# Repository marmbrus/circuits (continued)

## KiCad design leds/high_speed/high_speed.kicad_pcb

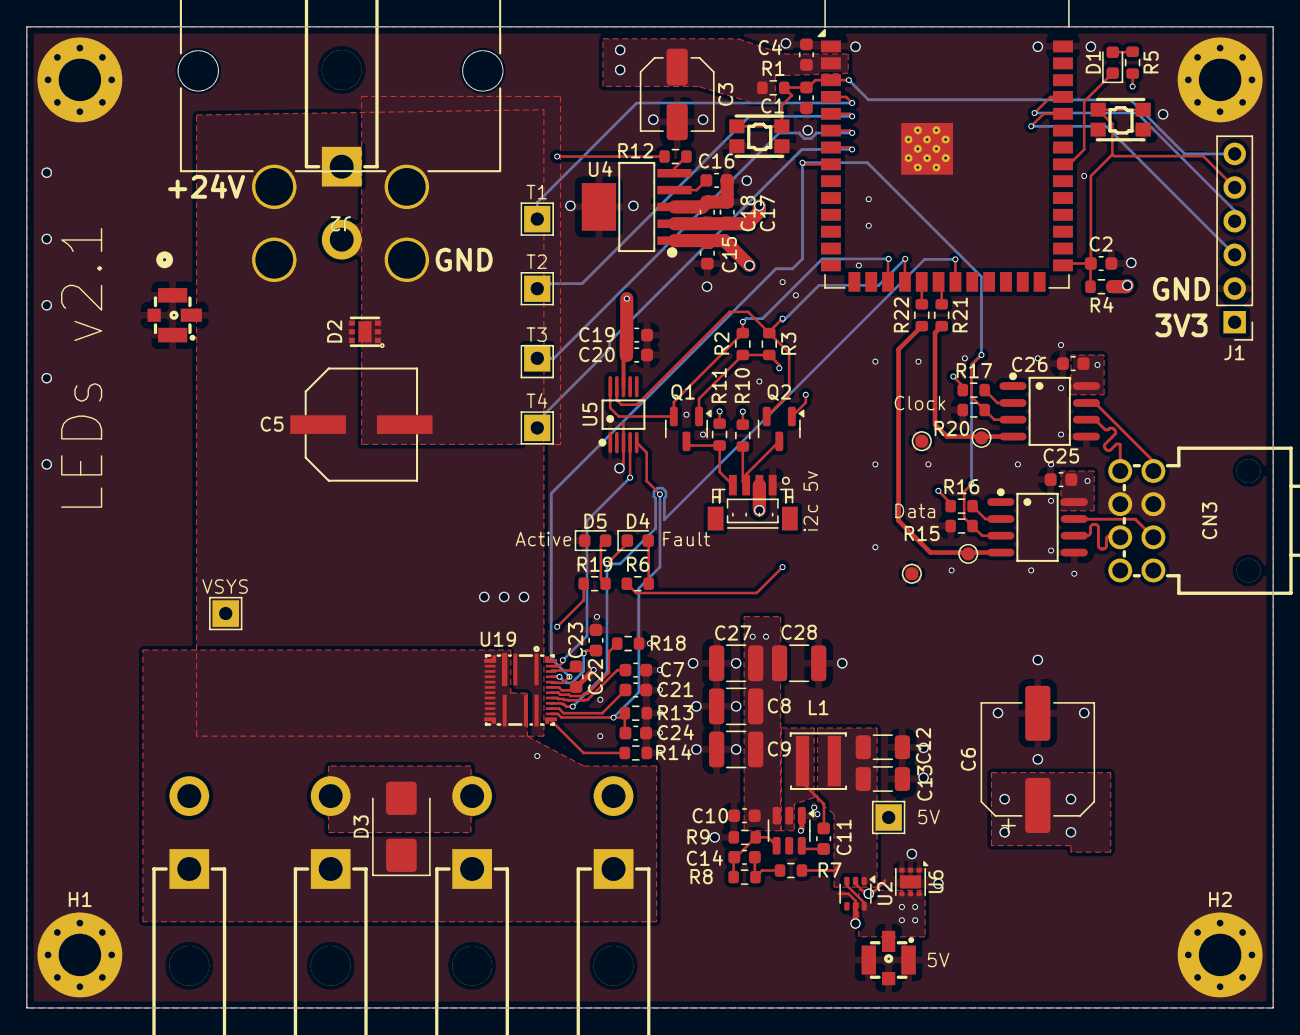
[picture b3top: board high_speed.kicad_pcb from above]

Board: 4 copper layers, 94.0 x 74.0 mm, 94 parts (0 on the bottom side), 48 nets.

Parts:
C1: 10uf; C_0603_1608Metric
C2: 1uf; C_0603_1608Metric
C3: 22uF; C_Elec_5x5.8
C4, C7, C10, C20, C24, C25, C26: 100nF; C_0603_1608Metric
C5: 220uF; CAP-SMD_BD8.0-L8.3-W8.3-FD
C6: C_Polarized; CP_Elec_8x11.9
C8, C9, C27, C28: 10uF; C_1210_3225Metric
C11: 100nf; C_0603_1608Metric
C12, C13: 22uF; C_1206_3216Metric
C14: 75pF; C_0603_1608Metric
C15, C17, C18, C19: 1uF; C_0603_1608Metric
C16: 10nF; C_0603_1608Metric
C21: 470nF; C_0603_1608Metric
C22, C23: 2.2uF; C_0603_1608Metric
CN1, CN2, CN5, CN6, CN13: 39-30-1020; CONN-TH_2P-P5.50_39-30-1020
CN3: 1053141108; CONN-TH_8P-P2.50_MOLEX_1053141108
CN4: BM04B-SRSS-TB(LF)(SN); CONN-SMD_BM04B-SRSS-TB
D1, D4, D5: LED; LED_0603_1608Metric
D2: TVS2700DRVR; WSON-6_L2.0-W2.0-P0.65-BL-EP
D3: D_TVS; D_SMB
H1, H2, H3, H4: MountingHole_Pad; MountingHole_3.2mm_M3_Pad_Via
J1: Conn_01x06; PinHeader_1x06_P2.54mm_Vertical
J2: 428202214; CONN_SDA-42820-0002_02_RC_MOL
L1: XAL4040-103MEC; IND-SMD_L4.0-W4.0-A
Q1, Q2: BSS138; SOT-23
R1, R2, R3, R4, R10, R11, R12, R15, R16, R17, R19, R20: 10k; R_0603_1608Metric
R5: 330; R_0603_1608Metric
R6: 1k; R_0603_1608Metric
R7: 49.9; R_0603_1608Metric
R8: 100k; R_0603_1608Metric
R9: 13.3k; R_0603_1608Metric
R13, R14: 3.6k; R_0603_1608Metric
R18: 53.6k; R_0603_1608Metric
R21, R22: 20; R_0603_1608Metric
RF1, RF2: 73412-0110; ANT-SMD_73412-0110
SW1, SW3: EVPAA602W; KEY-TH_4P-L3.5-W4.9-P2.80-LS4.3
TP1, TP6, TP7, TP8, TP9, TP14: LabeledTestPoint
TP2, TP3, TP4, TP5: TestPoint; TestPoint_Pad_D1.0mm
U1: ESP32-S3-WROOM-1
U2: LM66100DCK; SOT-363_SC-70-6
U3: TPS54202DDC; SOT-23-6
U4: TPS73733DCQ_C5220270; SOT-223-6_L6.5-W3.5-P1.27-LS7.0-BR
U5: ADS1115IDGSR; MSOP-10_L3.0-W3.0-P0.50-LS5.0-BL
U6: TVS0500DRV; WSON-6-1EP_2x2mm_P0.65mm_EP1x1.6mm
U7, U17: THVD2450DR; SOIC-8_L4.9-W3.9-P1.27-LS6.0-BL
U19: MP5048GU-Z; QFN-30_L5.0-W5.0-P0.40-TL_MP5048GU-Z

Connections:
/3v3/3v3: C3.1, C4.1, C17.1, C18.1, C25.1, C26.1, J1.1, Q1.1 (G), Q2.1 (G), R1.1, R2.1, R3.1, R4.1, R5.2, R6.1, R16.1, R17.1, U1.2 (3V3), U4.2 (OUT), U7.8 (VCC), U17.8 (VCC)
/5V: C6.1, C15.1, C19.1, C20.1, CN4.2, R10.1, R11.1, R12.1, RF2.2 (SIG), U2.3 (~CE), U2.6 (VOUT), U4.1 (IN), U5.8 (VDD), U6.4 (IN), U6.5 (IN), U6.6 (IN)
/VSYS: C5.1, C8.1, C9.1, C10.1, C27.1, C28.1, CN6.1, D2.4 (IN), D2.5 (IN), D2.6 (IN), J2.1_1, J2.1_2, RF1.2 (SIG), TP1.1, U3.3 (VIN), U19.1 (VIN), U19.2 (VIN), U19.18 (VIN)
/a2d/AIN1: U5.4 (AIN0), U19.29 (VTEMP)
/a2d/AIN2: C24.1, R13.1, U5.5 (AIN1), U19.20 (IMON)
/a2d/I2C.SCL: Q1.2 (S), R2.2, U1.17 (IO9), U5.10 (SCL)
/a2d/I2C.SDA: Q2.2 (S), R3.2, U1.18 (IO10), U5.9 (SDA)
/buckconverter/FB: C14.1, R8.2, R9.1, U3.4 (FB)
/buckconverter/SW: C11.2, L1.1, U3.2 (SW)
/esp32/EN1: R15.1, R20.1, U1.8 (IO15), U7.3 (DE), U17.3 (DE), U19.26 (ON)
/esp32/Fault: D4.1 (K), U1.21 (IO13), U19.22 (FAULT)
/esp32/LEDCLOCK: R21.2, TP2.1, U7.4 (D)
/esp32/LEDDATA: R22.2, TP3.1, U17.4 (D)
/esp32/T1: TP6.1, U1.4 (IO4)
/esp32/T2: TP7.1, U1.5 (IO5)
/esp32/T3: TP8.1, U1.6 (IO6)
/esp32/T4: TP9.1, U1.7 (IO7)
/led_channel/RS485/A: CN3.3, U17.6 (A)
/led_channel/RS485/B: CN3.7, U17.7 (B)
/led_channel/RS486/A: CN3.1, U7.6 (A)
/led_channel/RS486/B: CN3.5, U7.7 (B)
/led_channel/VLED: CN1.1, CN2.1, CN3.4, CN3.8, CN5.1, CN13.1, D3.1 (K), R19.1, U19.3 (VOUT), U19.4 (VOUT), U19.5 (VOUT), U19.6 (VOUT), U19.7 (VOUT), U19.8 (VOUT), U19.9 (VOUT), U19.10 (VOUT), U19.11 (VOUT), U19.12 (VOUT), U19.13 (VOUT), U19.14 (VOUT), U19.15 (VOUT), U19.16 (VOUT), U19.17 (VOUT)
GND: C1.2, C2.2, C3.2, C4.2, C5.2, C6.2, C7.2, C8.2, C9.2, C10.2, C12.2, C13.2, C15.2, C16.2, C17.2, C18.2, C19.2, C20.2, C21.2, C22.2, C23.2, C24.2, C25.2, C26.2, C27.2, C28.2, CN1.2, CN2.2, CN3.2, CN3.6, CN4.1, CN5.2, CN6.2, CN13.2, D2.1 (GND), D2.2 (GND), D2.3 (GND), D2.7 (GND), D3.2 (A), D5.1 (K), H1.1, H2.1, H3.1, H4.1, J1.2, J2.2_1, J2.2_2, R9.2, R13.2, R14.2, R15.2, R18.2, R20.2, RF1.1 (GND), RF1.3 (GND), RF1.4 (GND), RF2.1 (GND), RF2.3 (GND), RF2.4 (GND), SW1.2, SW1.2', SW3.2, SW3.2', TP4.1, TP5.1, U1.1 (GND), U1.40 (GND), U1.41 (GND), U2.2 (GND), U2.5 (ST), U3.1 (GND), U4.3 (GND), U4.6 (GND), U5.1 (ADDR), U5.3 (GND), U6.1 (GND), U6.2 (GND), U6.3 (GND), U6.7 (GND), U7.5 (GND), U17.5 (GND), U19.25 (GND)
unnamed: C14.2, R7.2, R8.1
unnamed: D1.2 (A), R5.1
unnamed: D1.1 (K), U1.33 (IO40)
unnamed: D4.2 (A), R6.2
unnamed: D5.2 (A), R19.2
unnamed: J1.3, U1.36 (RXD0)
unnamed: J1.4, U1.37 (TXD0)
unnamed: C2.1, J1.5, R4.2, SW3.1, SW3.1', U1.27 (IO0)
unnamed: C1.1, J1.6, R1.2, SW1.1, SW1.1', U1.3 (EN)
unnamed: CN4.4, Q1.3 (D), R11.2
unnamed: CN4.3, Q2.3 (D), R10.2
unnamed: R22.1, U1.19 (IO11)
unnamed: R21.1, U1.20 (IO12)
unnamed: C12.1, C13.1, L1.2, R7.1, TP14.1, U2.1 (VIN)
unnamed: C11.1, U3.6 (BOOT)
unnamed: R12.2, U4.5 (EN)
unnamed: C16.1, U4.4 (NR/FB)
unnamed: R17.2, U7.2 (~RE)
unnamed: R16.2, U17.2 (~RE)
unnamed: C23.1, U19.27 (3V)
unnamed: R18.1, U19.24 (CLREF)
unnamed: R14.1, U19.19 (CS)
unnamed: C21.1, U19.21 (SS)
unnamed: C7.1, U19.23 (TIMER)
unnamed: C22.1, U19.28 (VCC)

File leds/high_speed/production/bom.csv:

Designator,Footprint,Quantity,Value,LCSC Part #
C1,0603,1,10uf,
"C10, C11, C20, C24, C25, C26, C4, C7",0603,8,100nF,
"C12, C13",1206,2,22uF,
C14,0603,1,75pF,
"C15, C17, C18, C19, C2",0603,5,1uF,
C16,0603,1,10nF,
C21,0603,1,470nF,
"C22, C23",0603,2,2.2uF,
"C27, C28, C8, C9",1210,4,10uF,C77102
C3,C_Elec_5x5.8,1,22uF,C336246
C5,CAP-SMD_BD8.0-L8.3-W8.3-FD,1,220uF,C2923769
C6,CP_Elec_8x11.9,1,C_Polarized,C542295
"CN1, CN13, CN2, CN5",CONN-TH_2P-P5.50_39-30-1020,4,39-30-1020,C240832
CN3,CONN-TH_8P-P2.50_MOLEX_1053141108,1,1053141108,C841208
CN4,CONN-SMD_BM04B-SRSS-TB,1,BM04B-SRSS-TB(LF)(SN),C160390
D1,0603,1,LED,C2290
D2,WSON-6_L2.0-W2.0-P0.65-BL-EP,1,TVS2700DRVR,C523797
D3,D_SMB,1,D_TVS,C178227
D4,0603,1,LED,C2286
D5,0603,1,LED,C118334
L1,IND-SMD_L4.0-W4.0-A,1,XAL4040-103MEC,C5144883
"Q1, Q2",SOT-23,2,BSS138,
"R1, R10, R11, R12, R15, R16, R17, R19, R2, R20, R3, R4",0603,12,10k,
"R13, R14",0603,2,3.6k,
R18,0603,1,53.6k,
"R21, R22",0603,2,20,
R5,0603,1,330,
R6,0603,1,1k,
R7,0603,1,49.9,
R8,0603,1,100k,
R9,0603,1,13.3k,
"SW1, SW3",KEY-TH_4P-L3.5-W4.9-P2.80-LS4.3,2,EVPAA602W,C79148
U1,ESP32-S3-WROOM-1,1,ESP32-S3-WROOM-1,C2913202
"U17, U7",SOIC-8_L4.9-W3.9-P1.27-LS6.0-BL,2,THVD2450DR,C2672621
U19,QFN-30_L5.0-W5.0-P0.40-TL_MP5048GU-Z,1,MP5048GU-Z,C3662777
U2,SOT-363_SC-70-6,1,LM66100DCK,
U3,SOT-23-6,1,TPS54202DDC,
U4,SOT-223-6_L6.5-W3.5-P1.27-LS7.0-BR,1,TPS73733DCQ_C5220270,C5220270
U5,MSOP-10_L3.0-W3.0-P0.50-LS5.0-BL,1,ADS1115IDGSR,C37593
U6,WSON-6-1EP_2x2mm_P0.65mm_EP1x1.6mm,1,TVS0500DRV,

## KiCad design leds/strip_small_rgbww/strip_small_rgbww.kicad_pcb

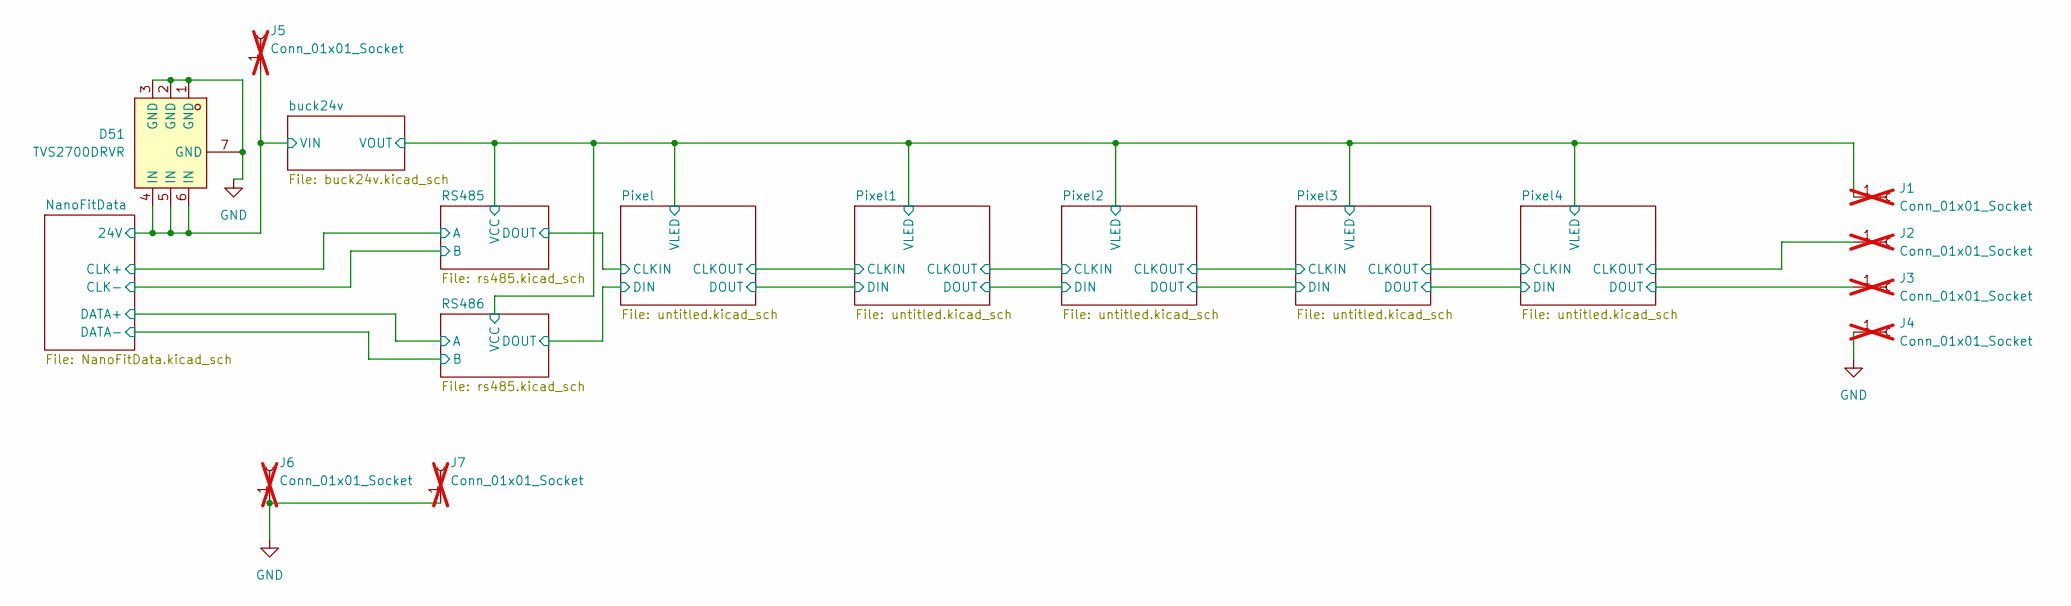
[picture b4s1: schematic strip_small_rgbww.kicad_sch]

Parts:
D51: TVS2700DRVR; WSON-6_L2.0-W2.0-P0.65-BL-EP; LCSC Part C523797
J1, J2, J3, J4, J5, J6, J7: Conn_01x01_Socket; SolderWirePad_1x01_SMD_2x4mm; not fitted

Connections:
/NanoFitData/24V: D51.4 (IN), D51.5 (IN), D51.6 (IN), J5.1; also elsewhere on the board
/Pixel4/CLKOUT: J2.1; also elsewhere on the board
/Pixel4/DOUT: J3.1; also elsewhere on the board
/Pixel/VLED: J1.1; also elsewhere on the board
GND: D51.1 (GND), D51.2 (GND), D51.3 (GND), D51.7 (GND), J4.1, J6.1, J7.1; also elsewhere on the board

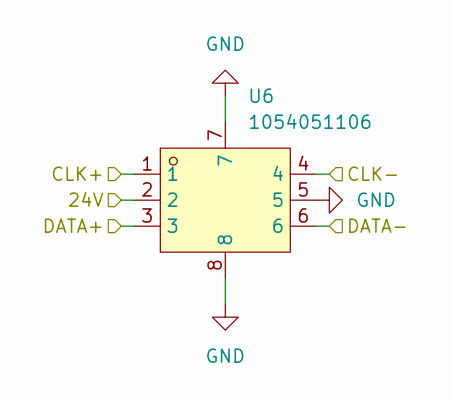
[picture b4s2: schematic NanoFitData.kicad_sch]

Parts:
U6: 1054051106; CONN-SMD_1054051106; LCSC Part C17285624

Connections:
/NanoFitData/24V: U6.2; also elsewhere on the board
/NanoFitData/CLK+: U6.1; also elsewhere on the board
/NanoFitData/CLK-: U6.4; also elsewhere on the board
/NanoFitData/DATA+: U6.3; also elsewhere on the board
/NanoFitData/DATA-: U6.6; also elsewhere on the board
GND: U6.5, U6.7, U6.8; also elsewhere on the board

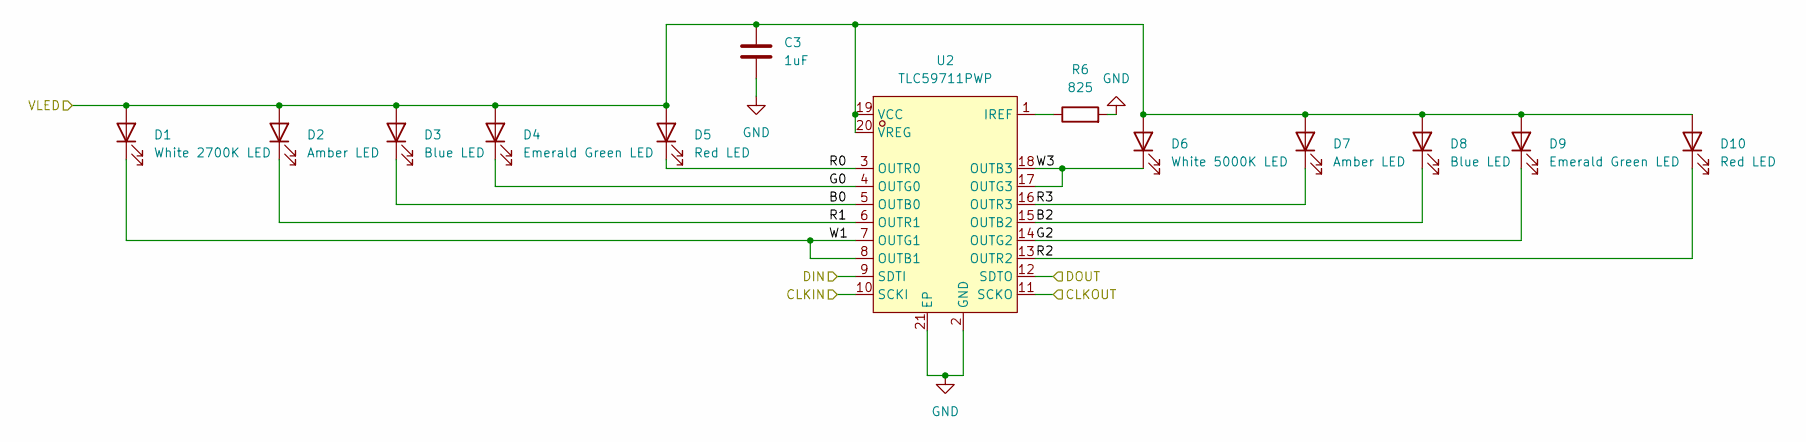
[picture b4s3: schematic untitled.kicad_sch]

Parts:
C3: 1uF; C_0603_1608Metric
D1: White 2700K LED; LED_PLCC_2835_Handsoldering; LCSC Part C17442107
D2, D7: Amber LED; LED-SMD_L3.2-W2.8-RD_YELLOW; LCSC Part C1322330
D3, D8: Blue LED; LED_PLCC_2835_Handsoldering; LCSC Part C2843871
D4, D9: Emerald Green LED; LED_PLCC_2835_Handsoldering; LCSC Part C2843870
D5, D10: Red LED; LED-SMD_L3.5-W2.8-RD-B; LCSC Part C5246339
D6: White 5000K LED; LED_PLCC_2835_Handsoldering; LCSC Part C5220761
R6: 825; R_0603_1608Metric
U2: TLC59711PWP; HTSSOP-20_L6.5-W4.4-P0.65-LS6.4-BL-EP-1; LCSC Part C1554176

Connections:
/Pixel1/B0: D3.1 (K), U2.5 (OUTB0)
/Pixel1/B2: D8.1 (K), U2.15 (OUTB2)
/Pixel1/CLKOUT: U2.11 (SCKO); also elsewhere on the board
/Pixel1/DOUT: U2.12 (SDTO); also elsewhere on the board
/Pixel1/G0: D4.1 (K), U2.4 (OUTG0)
/Pixel1/G2: D9.1 (K), U2.14 (OUTG2)
/Pixel1/R0: D5.1 (K), U2.3 (OUTR0)
/Pixel1/R1: D2.1 (K), U2.6 (OUTR1)
/Pixel1/R2: D10.1 (K), U2.13 (OUTR2)
/Pixel1/R3: D7.1 (K), U2.16 (OUTR3)
/Pixel1/W1: D1.1 (K), U2.7 (OUTG1), U2.8 (OUTB1)
/Pixel1/W3: D6.1 (K), U2.17 (OUTG3), U2.18 (OUTB3)
/Pixel/CLKOUT: U2.10 (SCKI); also elsewhere on the board
/Pixel/DOUT: U2.9 (SDTI); also elsewhere on the board
/Pixel/VLED: C3.1, D1.2 (A), D2.2 (A), D3.2 (A), D4.2 (A), D5.2 (A), D6.2 (A), D7.2 (A), D8.2 (A), D9.2 (A), D10.2 (A), U2.19 (VCC), U2.20 (VREG); also elsewhere on the board
GND: C3.2, R6.2, U2.2 (GND), U2.21 (EP); also elsewhere on the board
unnamed: R6.1, U2.1 (IREF)

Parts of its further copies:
C4, C5, C8, C25: 1uF; C_0603_1608Metric
D11, D21, D31, D41: White 2700K LED; LED_PLCC_2835_Handsoldering; LCSC Part C17442107
D12, D17, D22, D27, D32, D37, D42, D47: Amber LED; LED-SMD_L3.2-W2.8-RD_YELLOW; LCSC Part C1322330
D13, D18, D23, D28, D33, D38, D43, D48: Blue LED; LED_PLCC_2835_Handsoldering; LCSC Part C2843871
D14, D19, D24, D29, D34, D39, D44, D49: Emerald Green LED; LED_PLCC_2835_Handsoldering; LCSC Part C2843870
D15, D20, D25, D30, D35, D40, D45, D50: Red LED; LED-SMD_L3.5-W2.8-RD-B; LCSC Part C5246339
D16, D26, D36, D46: White 5000K LED; LED_PLCC_2835_Handsoldering; LCSC Part C5220761
R7, R8, R14, R25: 825; R_0603_1608Metric
U3, U4, U7, U10: TLC59711PWP; HTSSOP-20_L6.5-W4.4-P0.65-LS6.4-BL-EP-1; LCSC Part C1554176

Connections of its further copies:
/Pixel1/CLKOUT: U3.10 (SCKI); also elsewhere on the board
/Pixel1/DOUT: U3.9 (SDTI); also elsewhere on the board
/Pixel2/B0: D13.1 (K), U3.5 (OUTB0)
/Pixel2/B2: D18.1 (K), U3.15 (OUTB2)
/Pixel2/CLKOUT: U3.11 (SCKO), U7.10 (SCKI)
/Pixel2/DOUT: U3.12 (SDTO), U7.9 (SDTI)
/Pixel2/G0: D14.1 (K), U3.4 (OUTG0)
/Pixel2/G2: D19.1 (K), U3.14 (OUTG2)
/Pixel2/R0: D15.1 (K), U3.3 (OUTR0)
/Pixel2/R1: D12.1 (K), U3.6 (OUTR1)
/Pixel2/R2: D20.1 (K), U3.13 (OUTR2)
/Pixel2/R3: D17.1 (K), U3.16 (OUTR3)
/Pixel2/W1: D11.1 (K), U3.7 (OUTG1), U3.8 (OUTB1)
/Pixel2/W3: D16.1 (K), U3.17 (OUTG3), U3.18 (OUTB3)
/Pixel3/B0: D33.1 (K), U7.5 (OUTB0)
/Pixel3/B2: D38.1 (K), U7.15 (OUTB2)
/Pixel3/CLKOUT: U7.11 (SCKO), U10.10 (SCKI)
/Pixel3/DOUT: U7.12 (SDTO), U10.9 (SDTI)
/Pixel3/G0: D34.1 (K), U7.4 (OUTG0)
/Pixel3/G2: D39.1 (K), U7.14 (OUTG2)
/Pixel3/R0: D35.1 (K), U7.3 (OUTR0)
/Pixel3/R1: D32.1 (K), U7.6 (OUTR1)
/Pixel3/R2: D40.1 (K), U7.13 (OUTR2)
/Pixel3/R3: D37.1 (K), U7.16 (OUTR3)
/Pixel3/W1: D31.1 (K), U7.7 (OUTG1), U7.8 (OUTB1)
/Pixel3/W3: D36.1 (K), U7.17 (OUTG3), U7.18 (OUTB3)
/Pixel4/B0: D43.1 (K), U10.5 (OUTB0)
/Pixel4/B2: D48.1 (K), U10.15 (OUTB2)
/Pixel4/CLKOUT: U10.11 (SCKO); also elsewhere on the board
/Pixel4/DOUT: U10.12 (SDTO); also elsewhere on the board
/Pixel4/G0: D44.1 (K), U10.4 (OUTG0)
/Pixel4/G2: D49.1 (K), U10.14 (OUTG2)
/Pixel4/R0: D45.1 (K), U10.3 (OUTR0)
/Pixel4/R1: D42.1 (K), U10.6 (OUTR1)
/Pixel4/R2: D50.1 (K), U10.13 (OUTR2)
/Pixel4/R3: D47.1 (K), U10.16 (OUTR3)
/Pixel4/W1: D41.1 (K), U10.7 (OUTG1), U10.8 (OUTB1)
/Pixel4/W3: D46.1 (K), U10.17 (OUTG3), U10.18 (OUTB3)
/Pixel/B0: D23.1 (K), U4.5 (OUTB0)
/Pixel/B2: D28.1 (K), U4.15 (OUTB2)
/Pixel/CLKIN: U4.10 (SCKI); also elsewhere on the board
/Pixel/CLKOUT: U4.11 (SCKO); also elsewhere on the board
/Pixel/DIN: U4.9 (SDTI); also elsewhere on the board
/Pixel/DOUT: U4.12 (SDTO); also elsewhere on the board
/Pixel/G0: D24.1 (K), U4.4 (OUTG0)
/Pixel/G2: D29.1 (K), U4.14 (OUTG2)
/Pixel/R0: D25.1 (K), U4.3 (OUTR0)
/Pixel/R1: D22.1 (K), U4.6 (OUTR1)
/Pixel/R2: D30.1 (K), U4.13 (OUTR2)
/Pixel/R3: D27.1 (K), U4.16 (OUTR3)
/Pixel/VLED: C4.1, C5.1, C8.1, C25.1, D11.2 (A), D12.2 (A), D13.2 (A), D14.2 (A), D15.2 (A), D16.2 (A), D17.2 (A), D18.2 (A), D19.2 (A), D20.2 (A), D21.2 (A), D22.2 (A), D23.2 (A), D24.2 (A), D25.2 (A), D26.2 (A), D27.2 (A), D28.2 (A), D29.2 (A), D30.2 (A), D31.2 (A), D32.2 (A), D33.2 (A), D34.2 (A), D35.2 (A), D36.2 (A), D37.2 (A), D38.2 (A), D39.2 (A), D40.2 (A), D41.2 (A), D42.2 (A), D43.2 (A), D44.2 (A), D45.2 (A), D46.2 (A), D47.2 (A), D48.2 (A), D49.2 (A), D50.2 (A), U3.19 (VCC), U3.20 (VREG), U4.19 (VCC), U4.20 (VREG), U7.19 (VCC), U7.20 (VREG), U10.19 (VCC), U10.20 (VREG); also elsewhere on the board
/Pixel/W1: D21.1 (K), U4.7 (OUTG1), U4.8 (OUTB1)
/Pixel/W3: D26.1 (K), U4.17 (OUTG3), U4.18 (OUTB3)
GND: C4.2, C5.2, C8.2, C25.2, R7.2, R8.2, R14.2, R25.2, U3.2 (GND), U3.21 (EP), U4.2 (GND), U4.21 (EP), U7.2 (GND), U7.21 (EP), U10.2 (GND), U10.21 (EP); also elsewhere on the board
unnamed: R7.1, U3.1 (IREF)
unnamed: R8.1, U4.1 (IREF)
unnamed: R14.1, U7.1 (IREF)
unnamed: R25.1, U10.1 (IREF)

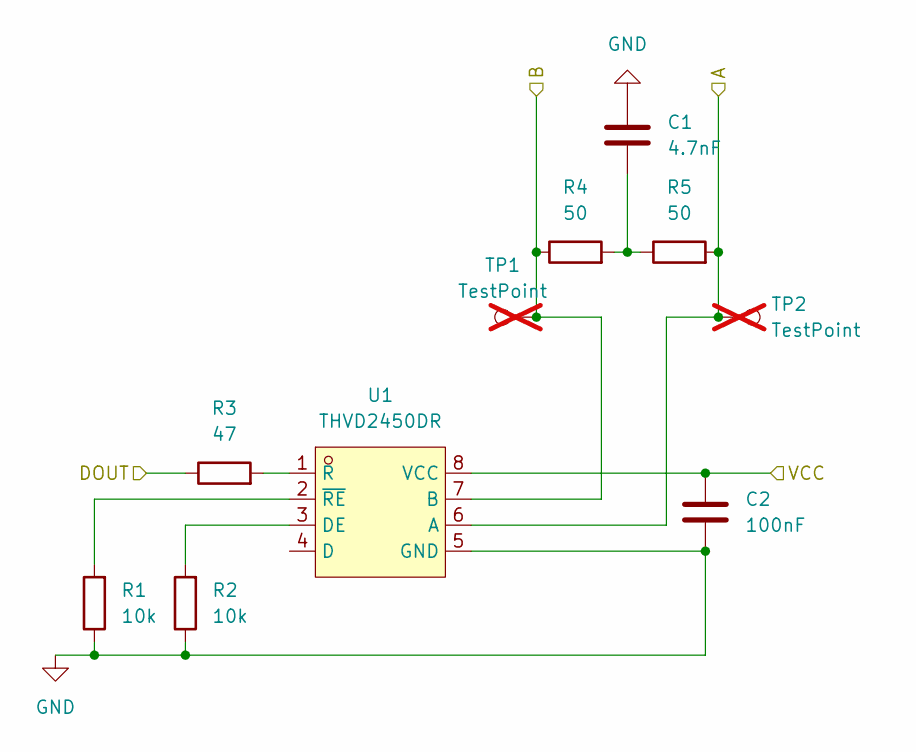
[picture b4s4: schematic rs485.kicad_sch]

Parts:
C1: 4.7nF; C_0402_1005Metric
C2: 100nF; C_0603_1608Metric
R1, R2: 10k; R_0402_1005Metric
R3: 47; R_0402_1005Metric
R4, R5: 50; R_0603_1608Metric
TP1, TP2: TestPoint; TestPoint_Pad_D1.0mm; not fitted
U1: THVD2450DR; SOIC-8_L4.9-W3.9-P1.27-LS6.0-BL; LCSC Part C2672621

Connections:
/NanoFitData/DATA+: R5.2, TP2.1, U1.6 (A); also elsewhere on the board
/NanoFitData/DATA-: R4.1, TP1.1, U1.7 (B); also elsewhere on the board
/Pixel/DIN: R3.1; also elsewhere on the board
/Pixel/VLED: C2.1, U1.8 (VCC); also elsewhere on the board
GND: C1.1, C2.2, R1.1, R2.1, U1.5 (GND); also elsewhere on the board
unnamed: C1.2, R4.2, R5.1
unnamed: R2.2, U1.3 (DE)
unnamed: R3.2, U1.1 (R)
unnamed: R1.2, U1.2 (~RE)

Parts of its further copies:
C6: 4.7nF; C_0402_1005Metric
C7: 100nF; C_0603_1608Metric
R9, R10: 10k; R_0402_1005Metric
R11: 47; R_0402_1005Metric
R12, R13: 50; R_0603_1608Metric
TP3, TP4: TestPoint; TestPoint_Pad_D1.0mm; not fitted
U5: THVD2450DR; SOIC-8_L4.9-W3.9-P1.27-LS6.0-BL; LCSC Part C2672621

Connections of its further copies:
/NanoFitData/CLK+: R13.2, TP4.1, U5.6 (A); also elsewhere on the board
/NanoFitData/CLK-: R12.1, TP3.1, U5.7 (B); also elsewhere on the board
/Pixel/CLKIN: R11.1; also elsewhere on the board
/Pixel/VLED: C7.1, U5.8 (VCC); also elsewhere on the board
GND: C6.1, C7.2, R9.1, R10.1, U5.5 (GND); also elsewhere on the board
unnamed: C6.2, R12.2, R13.1
unnamed: R10.2, U5.3 (DE)
unnamed: R11.2, U5.1 (R)
unnamed: R9.2, U5.2 (~RE)

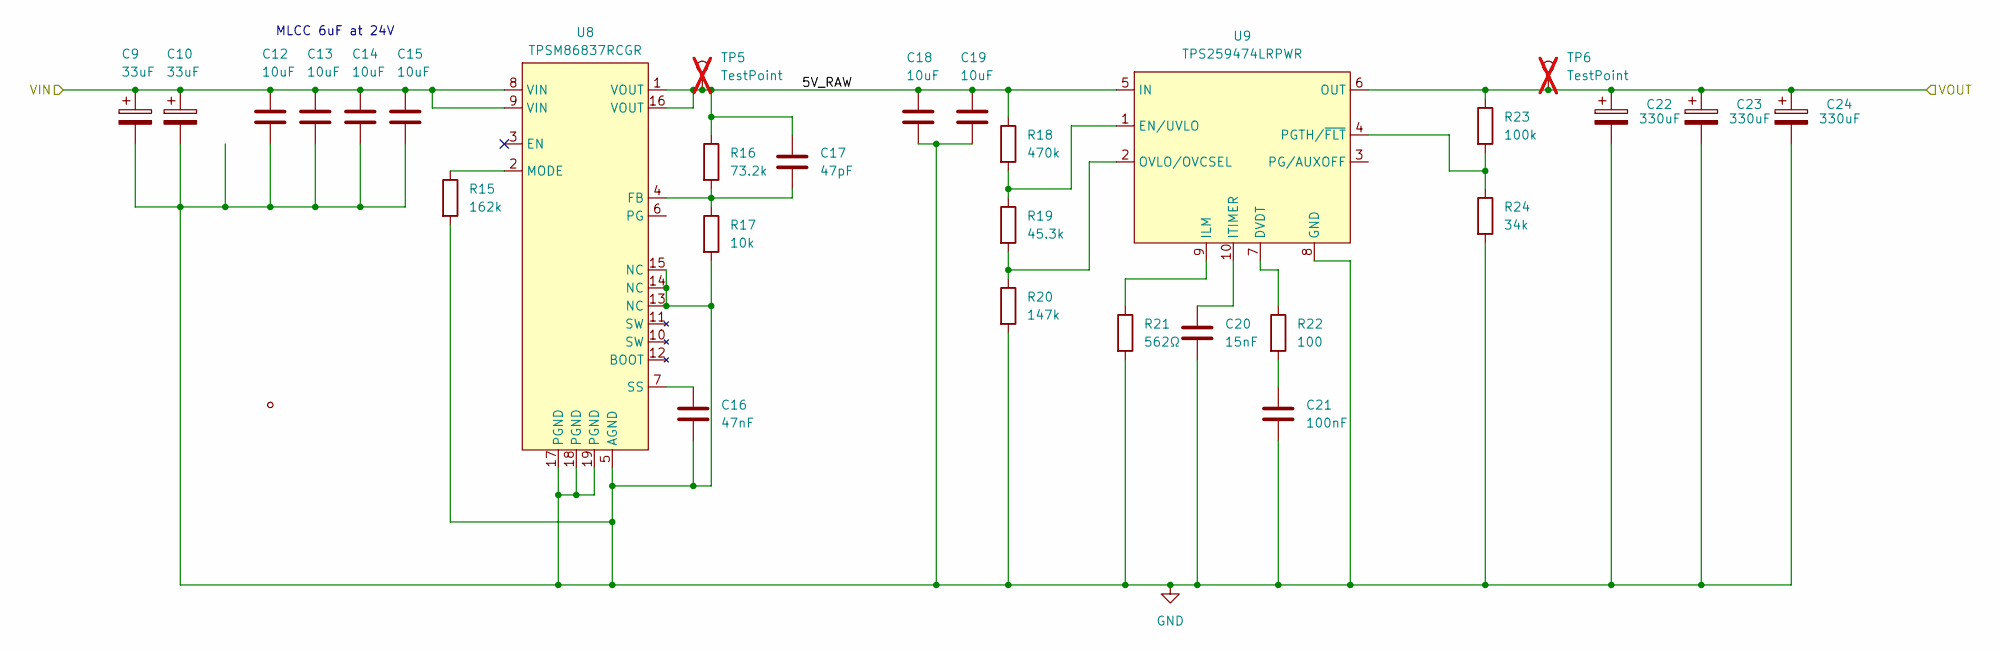
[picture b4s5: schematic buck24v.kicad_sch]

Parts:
C9, C10: 33uF; CP_EIA-7343-31_Kemet-D; LCSC Part C696815
C12, C13, C14, C15: 10uF; C_1210_3225Metric; LCSC Part C77102
C16: 47nF; C_0402_1005Metric
C17: 47pF; C_0402_1005Metric
C18, C19: 10uF; C_1206_3216Metric; LCSC Part C2803389
C20: 15nF; C_0402_1005Metric
C21: 100nF; C_0402_1005Metric
C22, C23, C24: 330uF; CAP-SMD_L7.3-W4.3-FD; LCSC Part C2159214
R15: 162k; R_0402_1005Metric
R16: 73.2k; R_0402_1005Metric
R17: 10k; R_0402_1005Metric
R18: 470k; R_0402_1005Metric
R19: 45.3k; R_0402_1005Metric
R20: 147k; R_0402_1005Metric
R21: 562Ω; R_0402_1005Metric
R22: 100; R_0402_1005Metric
R23: 100k; R_0402_1005Metric
R24: 34k; R_0402_1005Metric
TP5, TP6: TestPoint; TestPoint_Pad_D1.0mm; not fitted
U8: TPSM86837RCGR; B3QFN-19_L5.5-W5.0-P0.50-TL; LCSC Part C34572614
U9: TPS259474LRPWR; VQFN-10_L2.0-W2.0-P0.45-TL; LCSC Part C2864845

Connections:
/NanoFitData/24V: C9.1, C10.1, C12.1, C13.1, C14.1, C15.1, U8.8 (VIN), U8.9 (VIN); also elsewhere on the board
/Pixel/VLED: C22.1, C23.1, C24.1, R23.1, TP6.1, U9.6 (OUT); also elsewhere on the board
/buck24v/5V_RAW: C17.1, C18.1, C19.1, R16.1, R18.1, TP5.1, U8.1 (VOUT), U8.16 (VOUT), U9.5 (IN)
GND: C9.2, C10.2, C12.2, C13.2, C14.2, C15.2, C16.2, C18.2, C19.2, C20.2, C21.2, C22.2, C23.2, C24.2, R15.2, R17.2, R20.2, R21.2, R24.2, U8.5 (AGND), U8.13 (NC), U8.14 (NC), U8.15 (NC), U8.17 (PGND), U8.18 (PGND), U8.19 (PGND), U9.8 (GND); also elsewhere on the board
unnamed: C21.1, R22.2
unnamed: C17.2, R16.2, R17.1, U8.4 (FB)
unnamed: R15.1, U8.2 (MODE)
unnamed: C16.1, U8.7 (SS)
unnamed: R22.1, U9.7 (DVDT)
unnamed: R18.2, R19.1, U9.1 (EN/UVLO)
unnamed: R21.1, U9.9 (ILM)
unnamed: C20.1, U9.10 (ITIMER)
unnamed: R19.2, R20.1, U9.2 (OVLO/OVCSEL)
unnamed: R23.2, R24.1, U9.4 (PGTH/~FLT)

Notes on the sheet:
MLCC 6uF at 24V

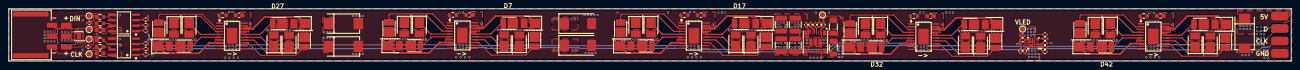
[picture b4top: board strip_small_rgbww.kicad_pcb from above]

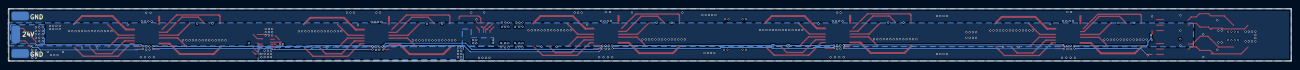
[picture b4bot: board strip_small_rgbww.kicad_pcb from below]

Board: 4 copper layers, 295.1 x 12.0 mm, 123 parts (3 on the bottom side), 93 nets.

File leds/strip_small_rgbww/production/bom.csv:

Designator,Footprint,Quantity,Value,LCSC Part #
"C1, C6",0402,2,4.7nF,
"C10, C9",CP_EIA-7343-31_Kemet-D,2,33uF,C696815
"C12, C13, C14, C15",1210,4,10uF,C77102
C16,0402,1,47nF,
C17,0402,1,47pF,
"C18, C19",1206,2,10uF,C2803389
"C2, C7",0603,2,100nF,
C20,0402,1,15nF,
C21,0402,1,100nF,
"C22, C23, C24",CAP-SMD_L7.3-W4.3-FD,3,330uF,C2159214
"C25, C3, C4, C5, C8",0603,5,1uF,
"D1, D11, D21, D31, D41",LED_PLCC_2835_Handsoldering,5,White 2700K LED,C17442107
"D10, D15, D20, D25, D30, D35, D40, D45, D5, D50",LED-SMD_L3.5-W2.8-RD-B,10,Red LED,C5246339
"D12, D17, D2, D22, D27, D32, D37, D42, D47, D7",LED-SMD_L3.2-W2.8-RD_YELLOW,10,Amber LED,C1322330
"D13, D18, D23, D28, D3, D33, D38, D43, D48, D8",LED_PLCC_2835_Handsoldering,10,Blue LED,C2843871
"D14, D19, D24, D29, D34, D39, D4, D44, D49, D9",LED_PLCC_2835_Handsoldering,10,Emerald Green LED,C2843870
"D16, D26, D36, D46, D6",LED_PLCC_2835_Handsoldering,5,White 5000K LED,C5220761
D51,WSON-6_L2.0-W2.0-P0.65-BL-EP,1,TVS2700DRVR,C523797
"R1, R10, R17, R2, R9",0402,5,10k,
"R11, R3",0402,2,47,
"R12, R13, R4, R5",0603,4,50,
"R14, R25, R6, R7, R8",0603,5,825,
R15,0402,1,162k,
R16,0402,1,73.2k,
R18,0402,1,470k,
R19,0402,1,45.3k,
R20,0402,1,147k,
R21,0402,1,562Ω,
R22,0402,1,100,
R23,0402,1,100k,
R24,0402,1,34k,
"U1, U5",SOIC-8_L4.9-W3.9-P1.27-LS6.0-BL,2,THVD2450DR,C2672621
"U10, U2, U3, U4, U7",HTSSOP-20_L6.5-W4.4-P0.65-LS6.4-BL-EP-1,5,TLC59711PWP,C1554176
U6,CONN-SMD_1054051106,1,1054051106,C17285624
U8,B3QFN-19_L5.5-W5.0-P0.50-TL,1,TPSM86837RCGR,C34572614
U9,VQFN-10_L2.0-W2.0-P0.45-TL,1,TPS259474LRPWR,C2864845

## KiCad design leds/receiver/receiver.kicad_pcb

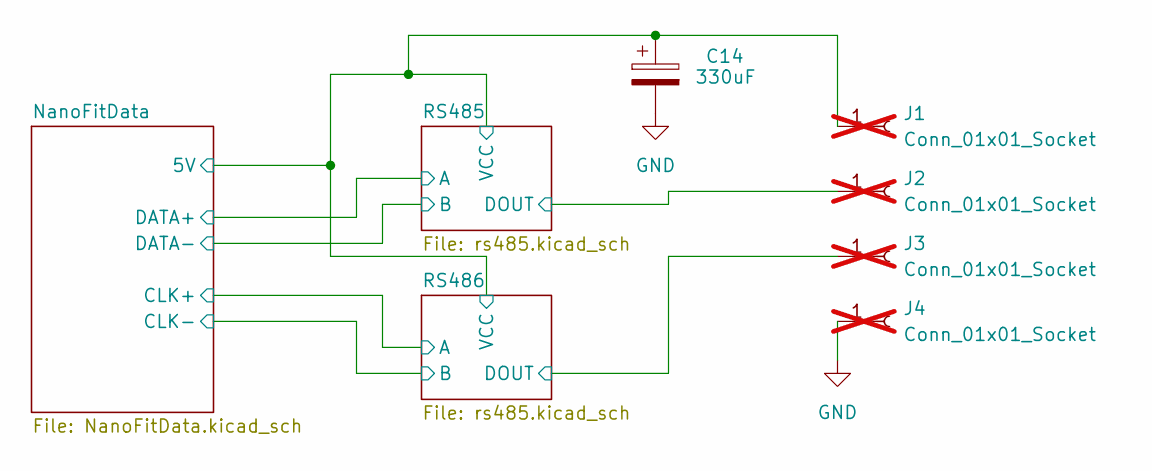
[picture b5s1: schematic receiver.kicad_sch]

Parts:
C14: 330uF; CAP-SMD_L7.3-W4.3-FD; LCSC Part C2159214
J1, J2, J3, J4: Conn_01x01_Socket; SolderWirePad_1x01_SMD_2x4mm; not fitted

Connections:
/NanoFitData/5V: C14.1, J1.1; also elsewhere on the board
/RS485/DOUT: J2.1; also elsewhere on the board
/RS486/DOUT: J3.1; also elsewhere on the board
GND: C14.2, J4.1; also elsewhere on the board

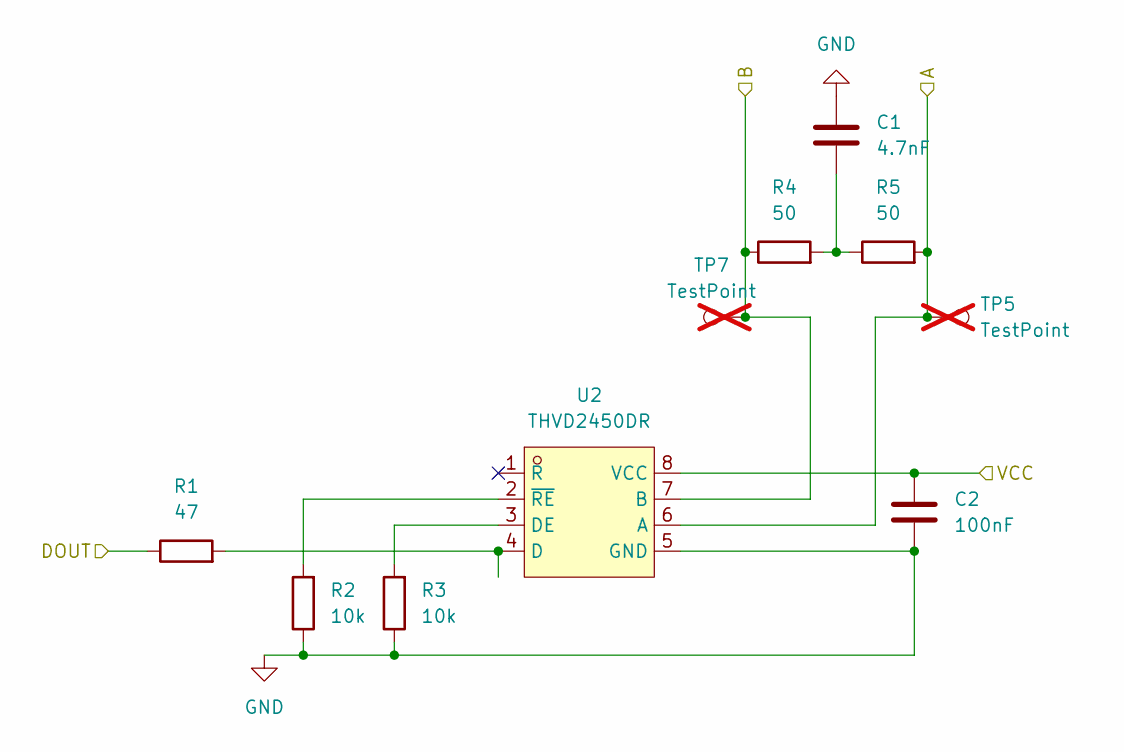
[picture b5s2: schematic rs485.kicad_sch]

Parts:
C1: 4.7nF; C_0402_1005Metric
C2: 100nF; C_0603_1608Metric
R1: 47; R_0402_1005Metric
R2, R3: 10k; R_0402_1005Metric
R4, R5: 50; R_0603_1608Metric
TP5, TP7: TestPoint; TestPoint_Pad_D1.0mm; not fitted
U2: THVD2450DR; SOIC-8_L4.9-W3.9-P1.27-LS6.0-BL; LCSC Part C2672621

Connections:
/NanoFitData/5V: C2.1, U2.8 (VCC); also elsewhere on the board
/NanoFitData/DATA+: R5.2, TP5.1, U2.6 (A); also elsewhere on the board
/NanoFitData/DATA-: R4.1, TP7.1, U2.7 (B); also elsewhere on the board
/RS485/DOUT: R1.1; also elsewhere on the board
GND: C1.1, C2.2, R2.1, R3.1, U2.5 (GND); also elsewhere on the board
unnamed: C1.2, R4.2, R5.1
unnamed: R1.2, U2.4 (D)
unnamed: R3.2, U2.3 (DE)
unnamed: R2.2, U2.2 (~RE)

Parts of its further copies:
C3: 4.7nF; C_0402_1005Metric
C4: 100nF; C_0603_1608Metric
R6: 47; R_0402_1005Metric
R7, R8: 10k; R_0402_1005Metric
R9, R10: 50; R_0603_1608Metric
TP6, TP8: TestPoint; TestPoint_Pad_D1.0mm; not fitted
U3: THVD2450DR; SOIC-8_L4.9-W3.9-P1.27-LS6.0-BL; LCSC Part C2672621

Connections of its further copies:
/NanoFitData/5V: C4.1, U3.8 (VCC); also elsewhere on the board
/NanoFitData/CLK+: R10.2, TP6.1, U3.6 (A); also elsewhere on the board
/NanoFitData/CLK-: R9.1, TP8.1, U3.7 (B); also elsewhere on the board
/RS486/DOUT: R6.1; also elsewhere on the board
GND: C3.1, C4.2, R7.1, R8.1, U3.5 (GND); also elsewhere on the board
unnamed: C3.2, R9.2, R10.1
unnamed: R6.2, U3.4 (D)
unnamed: R8.2, U3.3 (DE)
unnamed: R7.2, U3.2 (~RE)

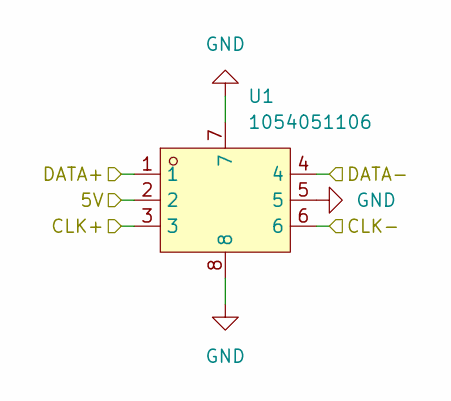
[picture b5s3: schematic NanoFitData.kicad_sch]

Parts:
U1: 1054051106; CONN-SMD_1054051106; LCSC Part C17285624

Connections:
/NanoFitData/5V: U1.2; also elsewhere on the board
/NanoFitData/CLK+: U1.3; also elsewhere on the board
/NanoFitData/CLK-: U1.6; also elsewhere on the board
/NanoFitData/DATA+: U1.1; also elsewhere on the board
/NanoFitData/DATA-: U1.4; also elsewhere on the board
GND: U1.5, U1.7, U1.8; also elsewhere on the board

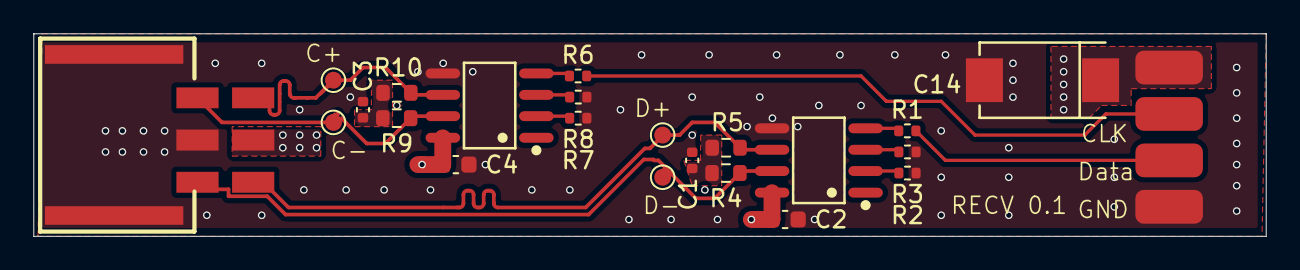
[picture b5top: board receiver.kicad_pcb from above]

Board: 4 copper layers, 73.0 x 12.0 mm, 26 parts (0 on the bottom side), 16 nets.

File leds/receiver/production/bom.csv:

Designator,Footprint,Quantity,Value,LCSC Part #
"C1, C3",0402,2,4.7nF,
C14,CAP-SMD_L7.3-W4.3-FD,1,330uF,C2159214
"C2, C4",0603,2,100nF,
"R1, R6",0402,2,47,
"R10, R4, R5, R9",0603,4,50,
"R2, R3, R7, R8",0402,4,10k,
U1,CONN-SMD_1054051106,1,1054051106,C17285624
"U2, U3",SOIC-8_L4.9-W3.9-P1.27-LS6.0-BL,2,THVD2450DR,C2672621

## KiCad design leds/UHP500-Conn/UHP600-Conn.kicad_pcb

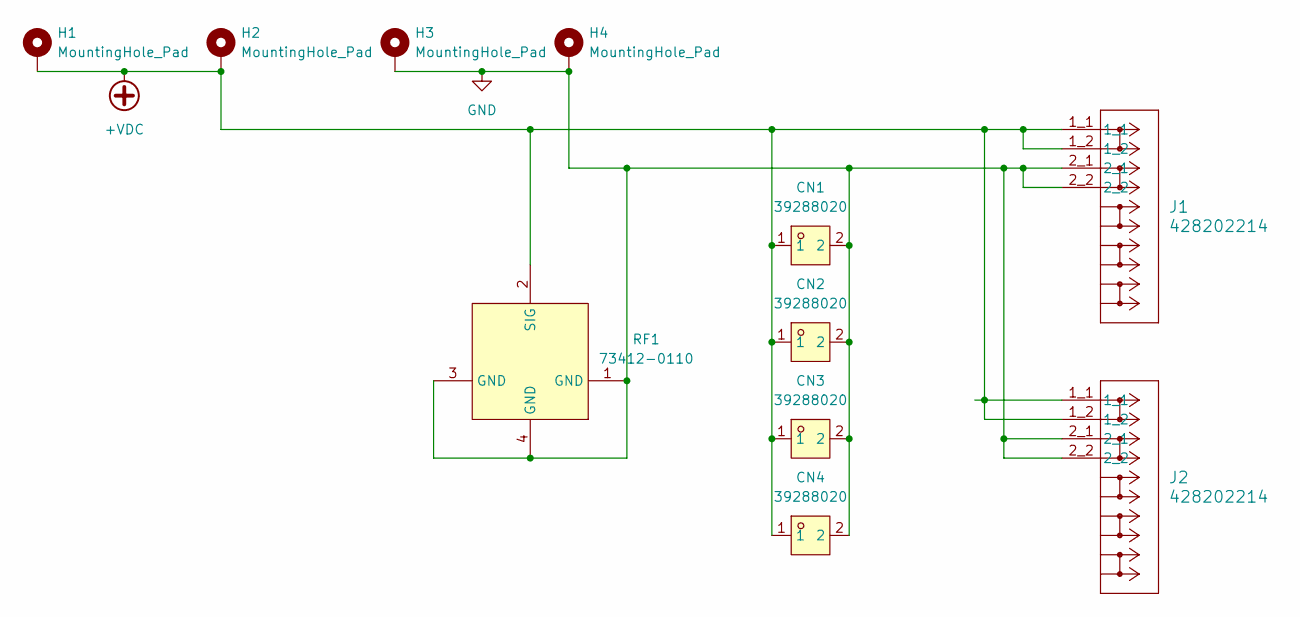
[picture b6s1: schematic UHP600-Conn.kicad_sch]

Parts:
CN1, CN2, CN3, CN4: 39288020; CONN-TH_39288020; LCSC Part C490534
H1, H2, H3, H4: MountingHole_Pad; MountingHole_4.3mm_M4_Pad_Via
J1, J2: 428202214; CONN_SDA-42820-0002_02_RC_MOL
RF1: 73412-0110; ANT-SMD_73412-0110; LCSC Part C434806

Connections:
+VDC: CN1.1, CN2.1, CN3.1, CN4.1, H1.1, H2.1, J1.1_1, J1.1_2, J2.1_1, J2.1_2, RF1.2 (SIG)
GND: CN1.2, CN2.2, CN3.2, CN4.2, H3.1, H4.1, J1.2_1, J1.2_2, J2.2_1, J2.2_2, RF1.1 (GND), RF1.3 (GND), RF1.4 (GND)

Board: 2 copper layers, 11 parts (0 on the bottom side), 2 nets, no tracks yet.

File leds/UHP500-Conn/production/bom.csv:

Designator,Footprint,Quantity,Value,LCSC Part #
"CN1, CN2, CN3, CN4",CONN-TH_39288020,4,39288020,C490534
"J1, J2",CONN_SDA-42820-0002_02_RC_MOL,2,428202214,
RF1,ANT-SMD_73412-0110,1,73412-0110,C434806
